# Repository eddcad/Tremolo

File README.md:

Clone of Lovetone's Wobbulator edited to fit in a Hammond 1590xx.

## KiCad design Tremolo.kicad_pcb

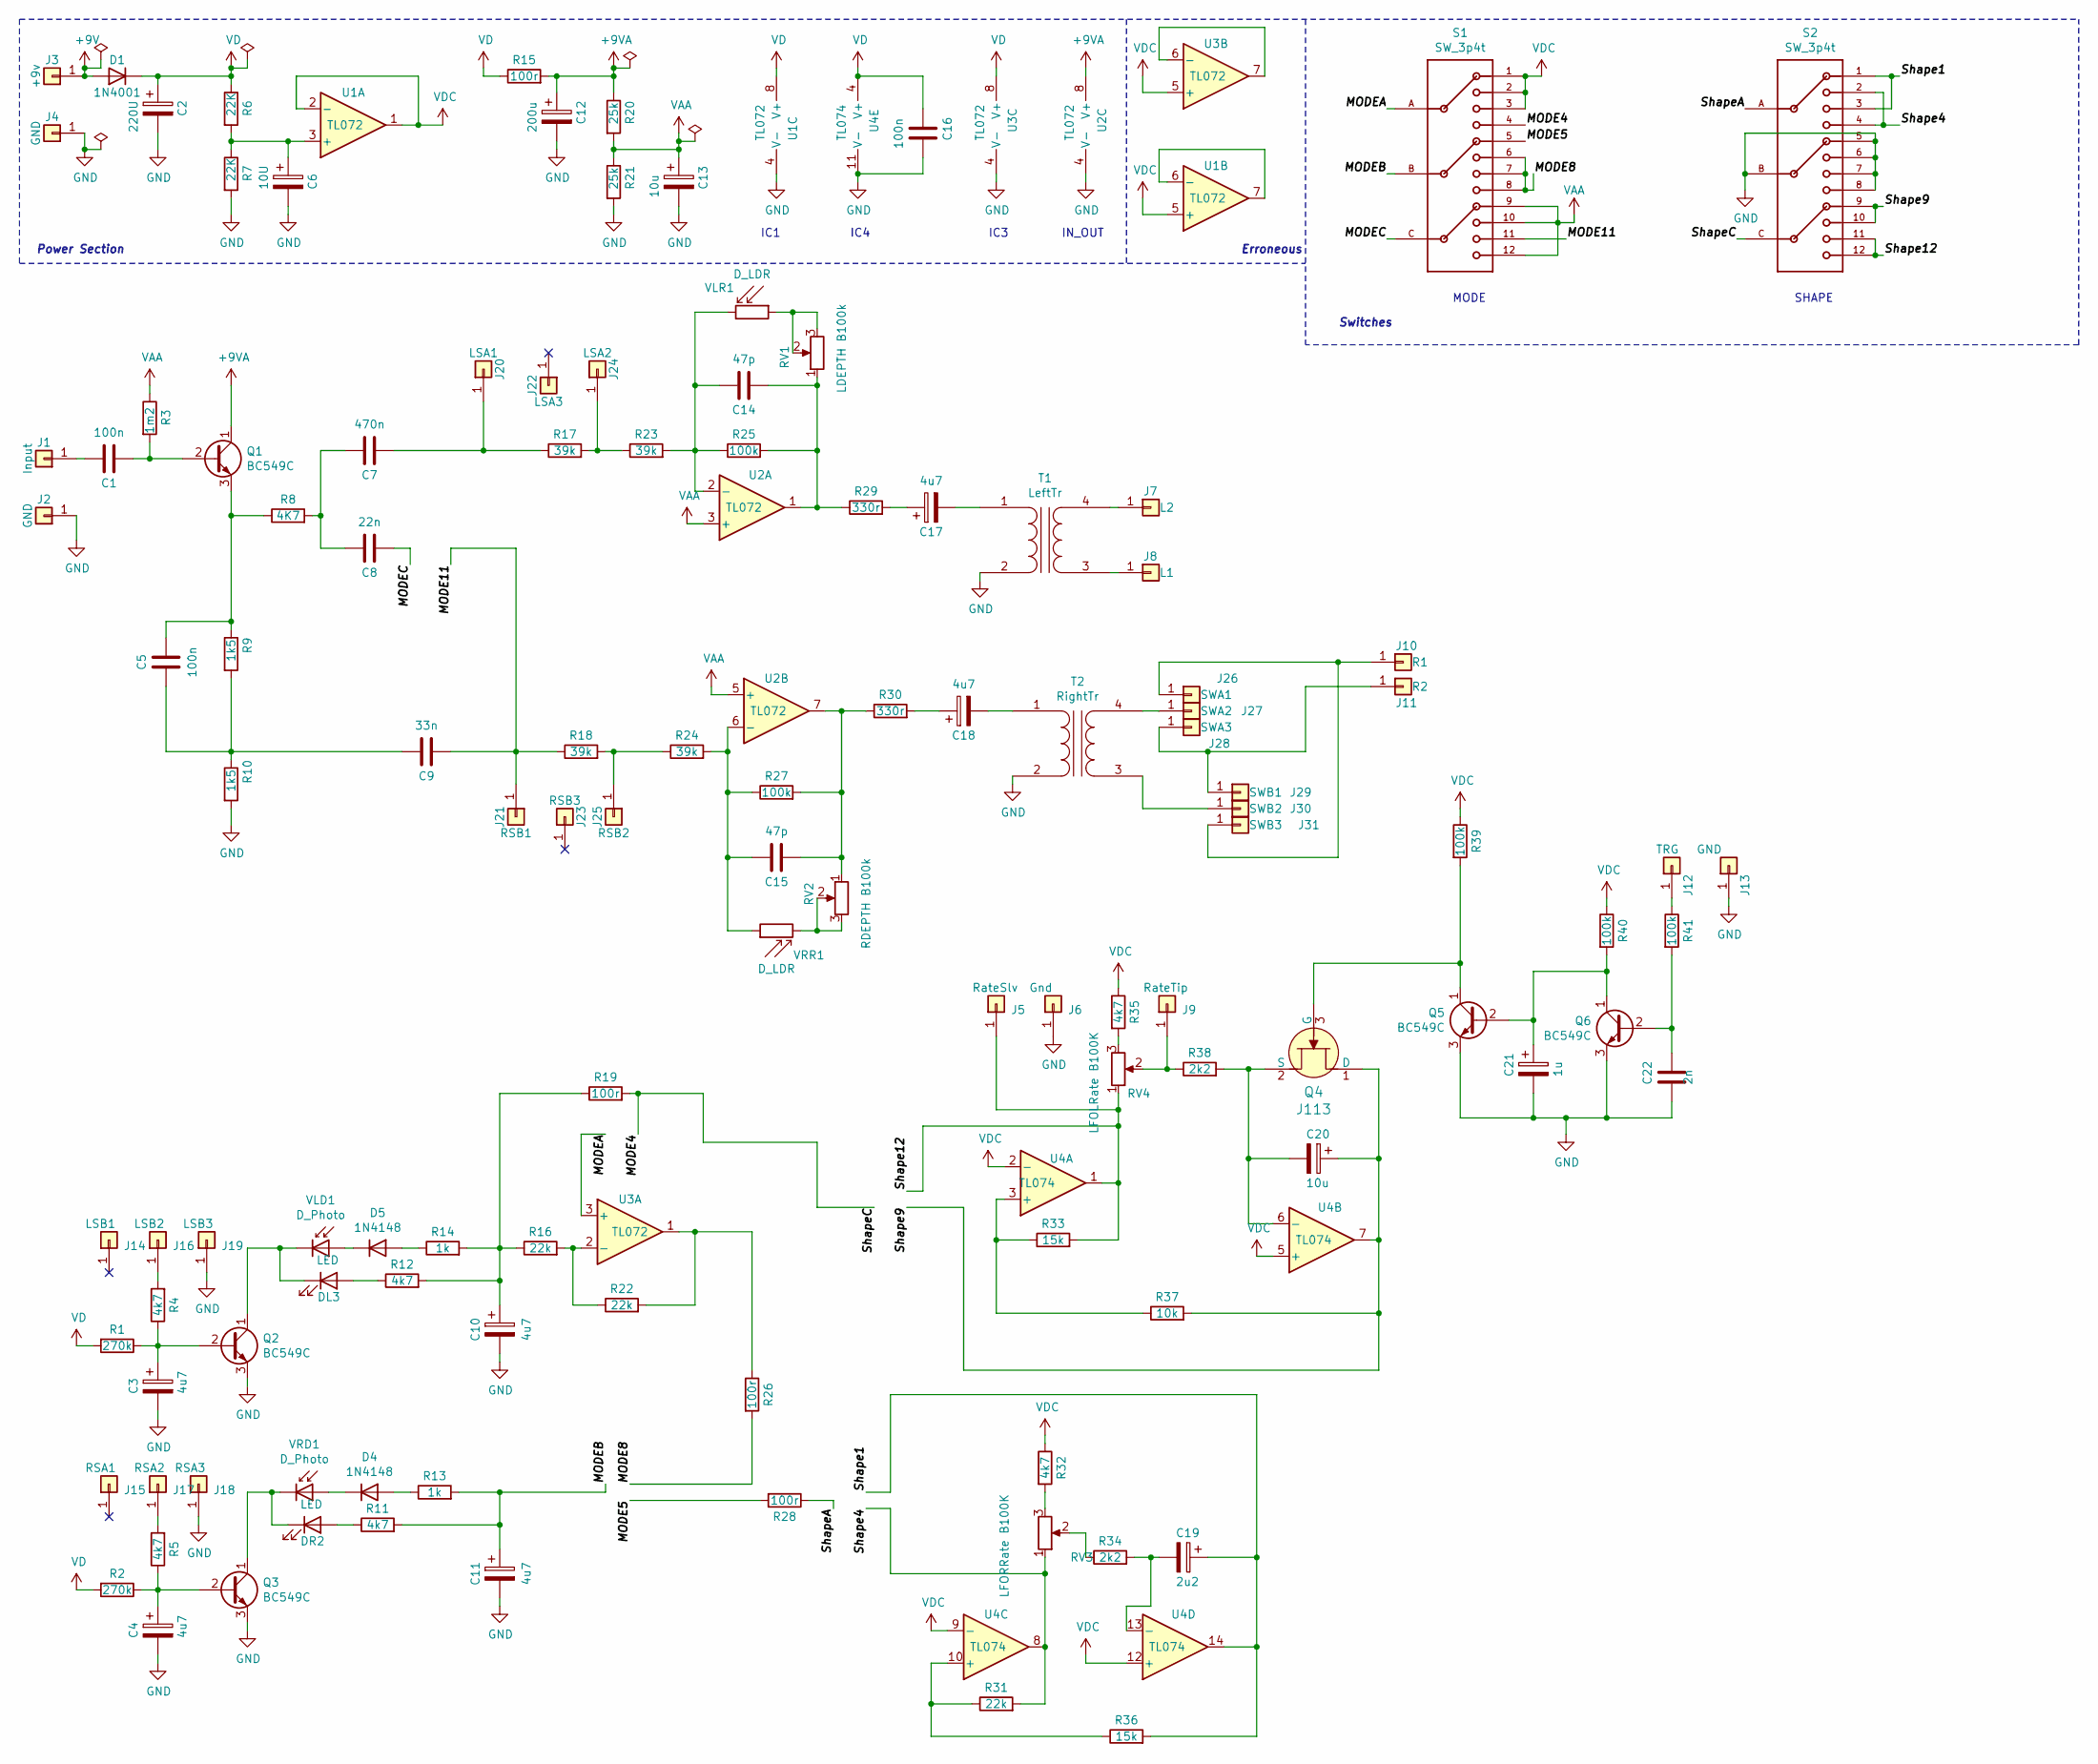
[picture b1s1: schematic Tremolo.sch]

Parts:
C1, C5, C16: 100n; C_Rect_L7.0mm_W2.5mm_P5.00mm
C2: 220U; CP_Radial_D6.3mm_P2.50mm
C3, C4, C10, C11, C17, C18: 4u7; CP_Radial_D4.0mm_P2.00mm
C6: 10U; CP_Radial_D5.0mm_P2.00mm
C7: 470n; C_Rect_L7.0mm_W3.5mm_P5.00mm
C8: 22n; C_Rect_L7.0mm_W2.5mm_P5.00mm
C9: 33n; C_Rect_L7.0mm_W2.5mm_P5.00mm
C12: 200u; CP_Radial_D6.3mm_P2.50mm
C13, C20: 10u; CP_Radial_D5.0mm_P2.00mm
C14, C15: 47p; C_Disc_D3.0mm_W2.0mm_P2.50mm
C19: 2u2; CP_Radial_D5.0mm_P2.00mm
C21: 1u; CP_Radial_D5.0mm_P2.00mm
C22: 2n; C_Rect_L7.0mm_W2.5mm_P5.00mm
D1: 1N4001; D_DO-41_SOD81_P10.16mm_Horizontal
D4, D5: 1N4148; D_DO-35_SOD27_P7.62mm_Horizontal
DL3: LED; LED_D5.0mm
DR2: LED; LED_D5.0mm
J1: Input; SolderWire-0.25sqmm_1x01_D0.65mm_OD1.7mm
J2, J4, J13: GND; SolderWire-0.25sqmm_1x01_D0.65mm_OD1.7mm
J3: +9v; SolderWire-0.25sqmm_1x01_D0.65mm_OD1.7mm
J5: RateSlv; SolderWire-0.25sqmm_1x01_D0.65mm_OD1.7mm
J6: Gnd; SolderWire-0.25sqmm_1x01_D0.65mm_OD1.7mm
J7: L2; SolderWire-0.25sqmm_1x01_D0.65mm_OD1.7mm
J8: L1; SolderWire-0.25sqmm_1x01_D0.65mm_OD1.7mm
J9: RateTip; SolderWire-0.25sqmm_1x01_D0.65mm_OD1.7mm
J10: R1; SolderWire-0.25sqmm_1x01_D0.65mm_OD1.7mm
J11: R2; SolderWire-0.25sqmm_1x01_D0.65mm_OD1.7mm
J12: TRG; SolderWire-0.25sqmm_1x01_D0.65mm_OD1.7mm
J14: LSB1; SolderWire-0.25sqmm_1x01_D0.65mm_OD1.7mm
J15: RSA1; SolderWire-0.25sqmm_1x01_D0.65mm_OD1.7mm
J16: LSB2; SolderWire-0.25sqmm_1x01_D0.65mm_OD1.7mm
J17: RSA2; SolderWire-0.25sqmm_1x01_D0.65mm_OD1.7mm
J18: RSA3; SolderWire-0.25sqmm_1x01_D0.65mm_OD1.7mm
J19: LSB3; SolderWire-0.25sqmm_1x01_D0.65mm_OD1.7mm
J20: LSA1; SolderWire-0.25sqmm_1x01_D0.65mm_OD1.7mm
J21: RSB1; SolderWire-0.25sqmm_1x01_D0.65mm_OD1.7mm
J22: LSA3; SolderWire-0.25sqmm_1x01_D0.65mm_OD1.7mm
J23: RSB3; SolderWire-0.25sqmm_1x01_D0.65mm_OD1.7mm
J24: LSA2; SolderWire-0.25sqmm_1x01_D0.65mm_OD1.7mm
J25: RSB2; SolderWire-0.25sqmm_1x01_D0.65mm_OD1.7mm
J26: SWA1; SolderWire-0.25sqmm_1x01_D0.65mm_OD1.7mm
J27: SWA2; SolderWire-0.25sqmm_1x01_D0.65mm_OD1.7mm
J28: SWA3; SolderWire-0.25sqmm_1x01_D0.65mm_OD1.7mm
J29: SWB1; SolderWire-0.25sqmm_1x01_D0.65mm_OD1.7mm
J30: SWB2; SolderWire-0.25sqmm_1x01_D0.65mm_OD1.7mm
J31: SWB3; SolderWire-0.25sqmm_1x01_D0.65mm_OD1.7mm
Q1, Q2, Q3, Q5, Q6: BC549C; TO-92L_Inline_Wide
Q4: J113; TO-92L_Inline_Wide; MPN J113; Digi-Key_PN J113FS-ND
R1, R2: 270k; R_Axial_DIN0207_L6.3mm_D2.5mm_P7.62mm_Horizontal
R3: 1m2; R_Axial_DIN0207_L6.3mm_D2.5mm_P7.62mm_Horizontal
R4, R5, R11, R12, R32, R35: 4k7; R_Axial_DIN0207_L6.3mm_D2.5mm_P7.62mm_Horizontal
R6, R7: 22K; R_Axial_DIN0207_L6.3mm_D2.5mm_P7.62mm_Horizontal
R8: 4K7; R_Axial_DIN0207_L6.3mm_D2.5mm_P7.62mm_Horizontal
R9, R10: 1k5; R_Axial_DIN0207_L6.3mm_D2.5mm_P7.62mm_Horizontal
R13, R14: 1k; R_Axial_DIN0207_L6.3mm_D2.5mm_P7.62mm_Horizontal
R15, R19, R26, R28: 100r; R_Axial_DIN0207_L6.3mm_D2.5mm_P7.62mm_Horizontal
R16, R22, R31: 22k; R_Axial_DIN0207_L6.3mm_D2.5mm_P7.62mm_Horizontal
R17, R18, R23, R24: 39k; R_Axial_DIN0207_L6.3mm_D2.5mm_P7.62mm_Horizontal
R20, R21: 25k; R_Axial_DIN0207_L6.3mm_D2.5mm_P7.62mm_Horizontal
R25, R27, R39, R40, R41: 100k; R_Axial_DIN0207_L6.3mm_D2.5mm_P7.62mm_Horizontal
R29, R30: 330r; R_Axial_DIN0207_L6.3mm_D2.5mm_P7.62mm_Horizontal
R33, R36: 15k; R_Axial_DIN0207_L6.3mm_D2.5mm_P7.62mm_Horizontal
R34, R38: 2k2; R_Axial_DIN0207_L6.3mm_D2.5mm_P7.62mm_Horizontal
R37: 10k; R_Axial_DIN0207_L6.3mm_D2.5mm_P7.62mm_Horizontal
RV1: LDEPTH B100k; Potentiometer_Omeg_PC16BU_Vertical
RV2: RDEPTH B100k; Potentiometer_Omeg_PC16BU_Vertical
RV3: LFORRate B100K; Potentiometer_Omeg_PC16BU_Vertical
RV4: LFOLRate B100K; Potentiometer_Omeg_PC16BU_Vertical
S1, S2: SW_3p4t; 3p4tRotary
T1: LeftTr; OEP1200
T2: RightTr; OEP1200
U1, U2, U3: TL072; DIP-8_W7.62mm
U4: TL074; DIP-14_W7.62mm
VLD1: D_Photo; LED_D5.0mm
VLR1: D_LDR; R_LDR_5.2x5.2mm_P3.5mm_Horizontal
VRD1: D_Photo; LED_D5.0mm
VRR1: D_LDR; R_LDR_5.2x5.2mm_P3.5mm_Horizontal

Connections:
+9V: D1.2 (A), J3.1
+9VA: C12.1, Q1.1 (C), R15.2, R20.1, U2.8 (V+)
/MODE4: R19.2, S1.4, S2.C
/MODE5: R28.2, S1.5
/MODE8: R26.2, S1.6, S1.7, S1.8
/MODE11: C9.1, J21.1, R18.1, S1.11
/MODEA: S1.A, U3.3 (+)
/MODEB: C11.1, R11.2, R13.2, S1.B
/MODEC: C8.1, S1.C
/Shape1: C19.1, R36.2, S2.1, S2.3, U4.14
/Shape4: R31.2, RV3.1, S2.2, S2.4, U4.8
/Shape9: C20.1, Q4.1 (D), R37.2, S2.9, S2.10, U4.7
/Shape12: J5.1, R33.2, RV4.1, S2.11, S2.12, U4.1
/ShapeA: R28.1, S2.A
GND: C2.2, C3.2, C4.2, C6.2, C10.2, C11.2, C12.2, C13.2, C16.2, C21.2, C22.2, J2.1, J4.1, J6.1, J13.1, J18.1, J19.1, Q2.3 (E), Q3.3 (E), Q5.3 (E), Q6.3 (E), R7.2, R10.2, R21.2, S2.5, S2.6, S2.7, S2.8, S2.B, T1.2 (AB), T2.2 (AB), U1.4 (V-), U2.4 (V-), U3.4 (V-), U4.11 (V-)
unnamed: C1.1, Q1.2 (B), R3.2
unnamed: C1.2, J1.1
unnamed: C3.1, Q2.2 (B), R1.1, R4.1
unnamed: C4.1, Q3.2 (B), R2.1, R5.1
unnamed: C5.1, C9.2, R9.2, R10.1
unnamed: C5.2, Q1.3 (E), R8.1, R9.1
unnamed: C6.1, R6.2, R7.1, U1.3 (+)
unnamed: C7.1, J20.1, R17.1
unnamed: C7.2, C8.2, R8.2
unnamed: C10.1, R12.2, R14.2, R16.1, R19.1
unnamed: C14.1, R25.2, R29.1, RV1.1, U2.1
unnamed: C14.2, R23.2, R25.1, U2.2 (-), VLR1.2
unnamed: C15.1, R27.2, R30.1, RV2.1, U2.7
unnamed: C15.2, R24.2, R27.1, U2.6 (-), VRR1.1
unnamed: C17.1, R29.2
unnamed: C17.2, T1.1 (AA)
unnamed: C18.1, R30.2
unnamed: C18.2, T2.1 (AA)
unnamed: C19.2, R34.2, U4.13 (-)
unnamed: C20.2, Q4.2 (S), R38.2, U4.6 (-)
unnamed: C21.1, Q5.2 (B), Q6.1 (C), R40.2
unnamed: C22.1, Q6.2 (B), R41.2
unnamed: D4.1 (K), VRD1.2 (A)
unnamed: D4.2 (A), R13.1
unnamed: D5.1 (K), VLD1.2 (A)
unnamed: D5.2 (A), R14.1
unnamed: DL3.1 (K), Q2.1 (C), VLD1.1 (K)
unnamed: DL3.2 (A), R12.1
unnamed: DR2.1 (K), Q3.1 (C), VRD1.1 (K)
unnamed: DR2.2 (A), R11.1
unnamed: J7.1, T1.4 (SB)
unnamed: J8.1, T1.3 (SA)
unnamed: J9.1, R38.1, RV4.2
unnamed: J10.1, J26.1, J31.1
unnamed: J11.1, J28.1, J29.1
unnamed: J12.1, R41.1
unnamed: J16.1, R4.2
unnamed: J17.1, R5.2
unnamed: J24.1, R17.2, R23.1
unnamed: J25.1, R18.2, R24.1
unnamed: J27.1, T2.4 (SB)
unnamed: J30.1, T2.3 (SA)
unnamed: Q4.3 (G), Q5.1 (C), R39.2
unnamed: R16.2, R22.1, U3.2 (-)
unnamed: R22.2, R26.1, U3.1
unnamed: R31.1, R36.1, U4.10 (+)
unnamed: R32.2, RV3.3
unnamed: R33.1, R37.1, U4.3 (+)
unnamed: R34.1, RV3.2
unnamed: R35.2, RV4.3
unnamed: RV1.2, RV1.3, VLR1.1
unnamed: RV2.2, RV2.3, VRR1.2
unnamed: U1.6 (-), U1.7
unnamed: U3.6 (-), U3.7
VAA: C13.1, R3.1, R20.2, R21.1, S1.9, S1.10, S1.12, U2.3 (+), U2.5 (+)
VD: C2.1, C16.1, D1.1 (K), R1.2, R2.2, R6.1, R15.1, U1.8 (V+), U3.8 (V+), U4.4 (V+)
VDC: R32.1, R35.1, R39.1, R40.1, S1.1, S1.2, S1.3, U1.1, U1.2 (-), U1.5 (+), U3.5 (+), U4.2 (-), U4.5 (+), U4.9 (-), U4.12 (+)

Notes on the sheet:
Power Section
IC1
IC4
IC3
IN_OUT
MODE
SHAPE
Switches
Erroneous

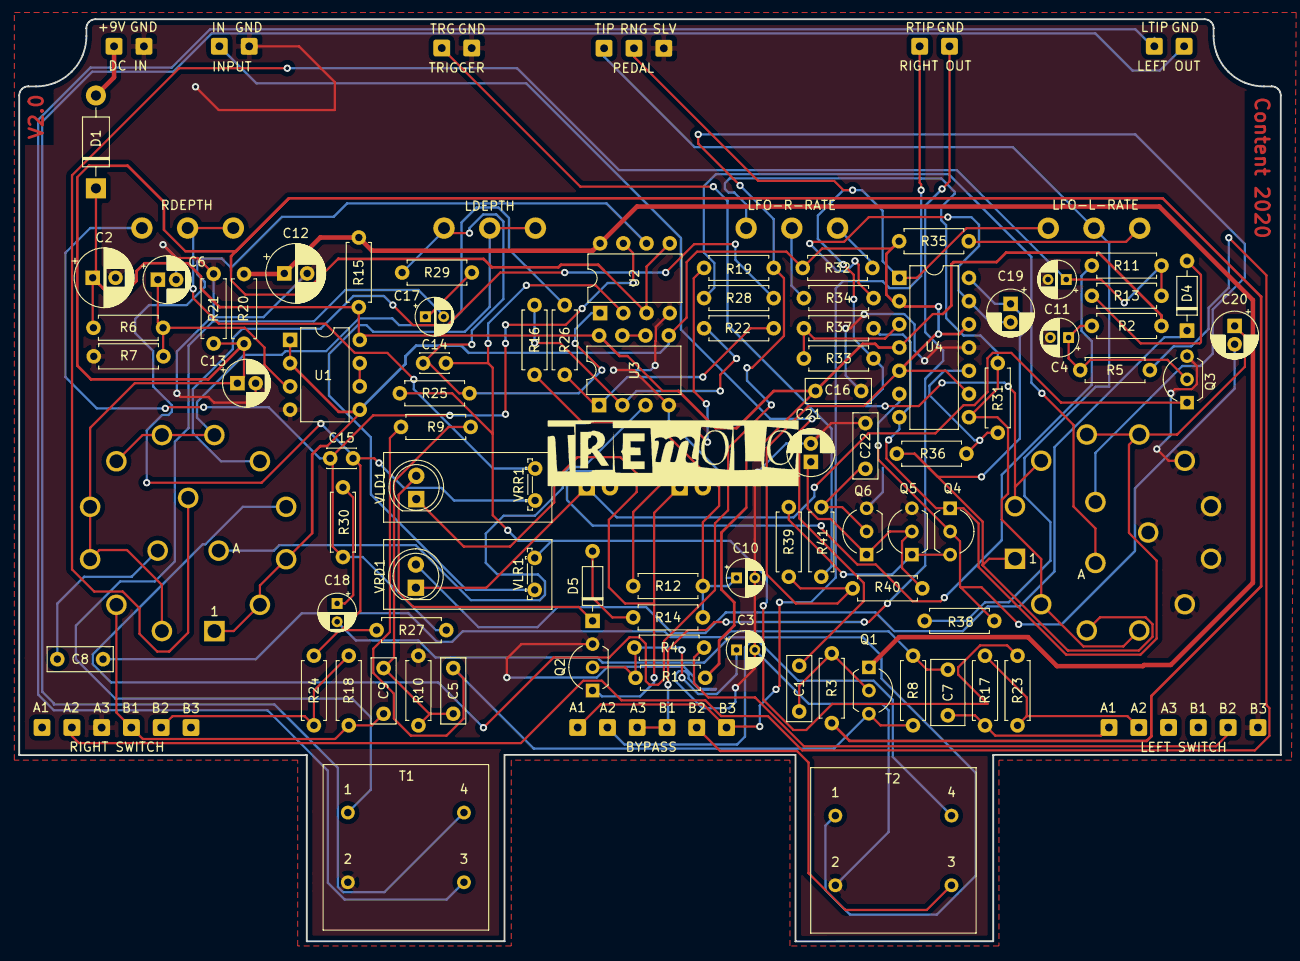
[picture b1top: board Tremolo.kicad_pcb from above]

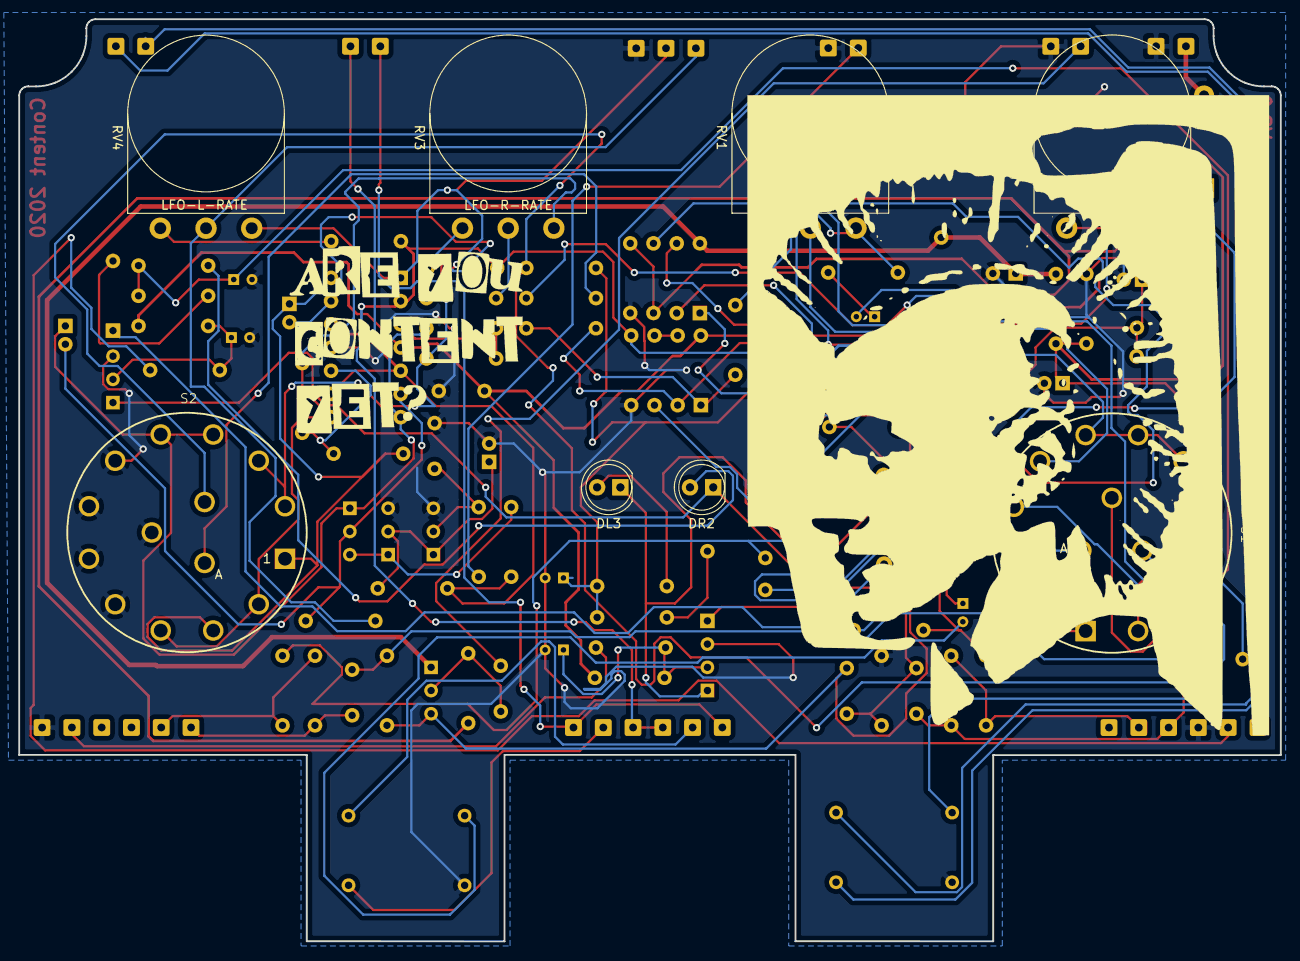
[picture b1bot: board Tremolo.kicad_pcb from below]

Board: 2 copper layers, 138.0 x 100.9 mm, 121 parts (8 on the bottom side), 72 nets.

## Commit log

2020-09-12 Changed version number to V1.2
2020-09-12 Added newline ti gitignore
2020-09-14 Removed extra logo footprints
2020-09-21 Updated .gitignore
2020-09-21 V2.0 provisionaly completed
2020-09-21 edited .gitignore
2020-11-07 License added
2020-11-07 Initial edit of README, more to come.
2020-11-07 Removed untracked files
